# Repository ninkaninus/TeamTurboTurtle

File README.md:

# TeamTurboTurtle
This is the repository of Team Turbo Turtle! A group made for the second semester project in robotics technology at Southern University Of Denmark. The goal of the project is to automate a scalextric car to run the fastest lap on an unknown course all by itself.

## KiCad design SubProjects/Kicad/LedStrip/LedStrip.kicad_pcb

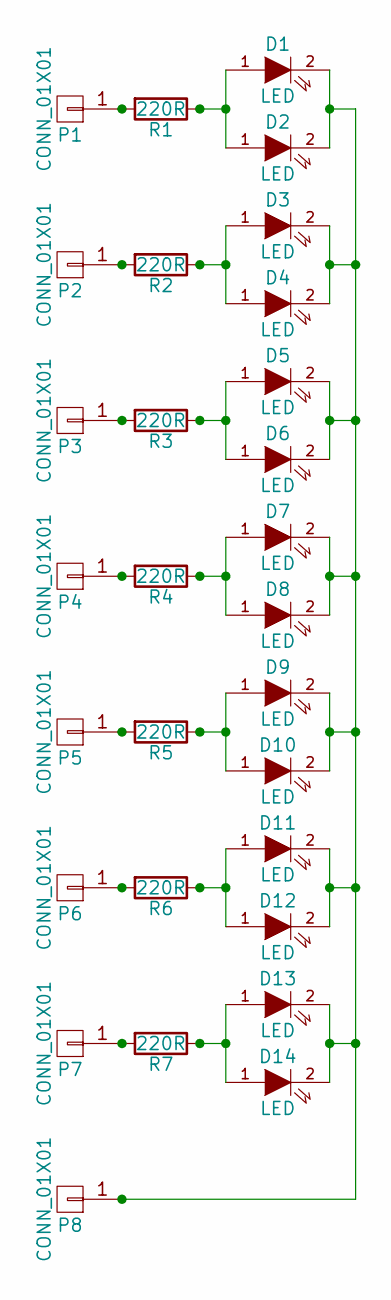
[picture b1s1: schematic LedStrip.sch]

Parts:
D1, D2, D3, D4, D5, D6, D7, D8, D9, D10, D11, D12, D13, D14: LED; LED-0805
P1, P2, P3, P4, P5, P6, P7, P8: CONN_01X01; Pin_Header_Straight_1x01
R1, R2, R3, R4, R5, R6, R7: 220R; R_0805_HandSoldering

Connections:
unnamed: D1.1 (A), D2.1 (A), R1.1
unnamed: D1.2 (K), D2.2 (K), D3.2 (K), D4.2 (K), D5.2 (K), D6.2 (K), D7.2 (K), D8.2 (K), D9.2 (K), D10.2 (K), D11.2 (K), D12.2 (K), D13.2 (K), D14.2 (K), P8.1
unnamed: D3.1 (A), D4.1 (A), R2.1
unnamed: D5.1 (A), D6.1 (A), R3.1
unnamed: D7.1 (A), D8.1 (A), R4.1
unnamed: D9.1 (A), D10.1 (A), R5.1
unnamed: D11.1 (A), D12.1 (A), R6.1
unnamed: D13.1 (A), D14.1 (A), R7.1
unnamed: P1.1, R1.2
unnamed: P2.1, R2.2
unnamed: P3.1, R3.2
unnamed: P4.1, R4.2
unnamed: P5.1, R5.2
unnamed: P6.1, R6.2
unnamed: P7.1, R7.2

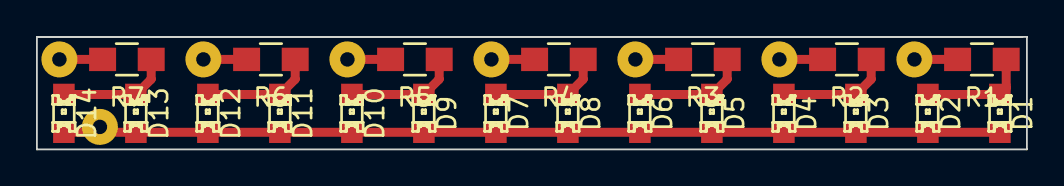
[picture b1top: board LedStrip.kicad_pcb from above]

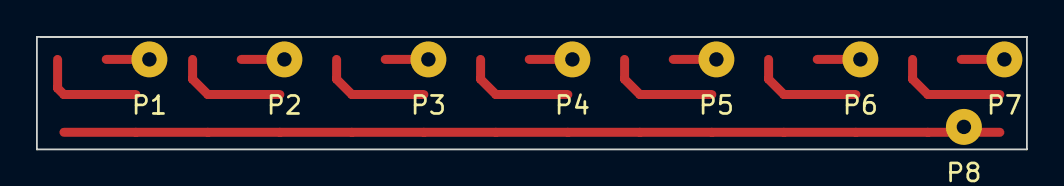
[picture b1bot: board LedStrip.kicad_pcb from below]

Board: 2 copper layers, 55.0 x 6.2 mm, 29 parts (8 on the bottom side), 15 nets.

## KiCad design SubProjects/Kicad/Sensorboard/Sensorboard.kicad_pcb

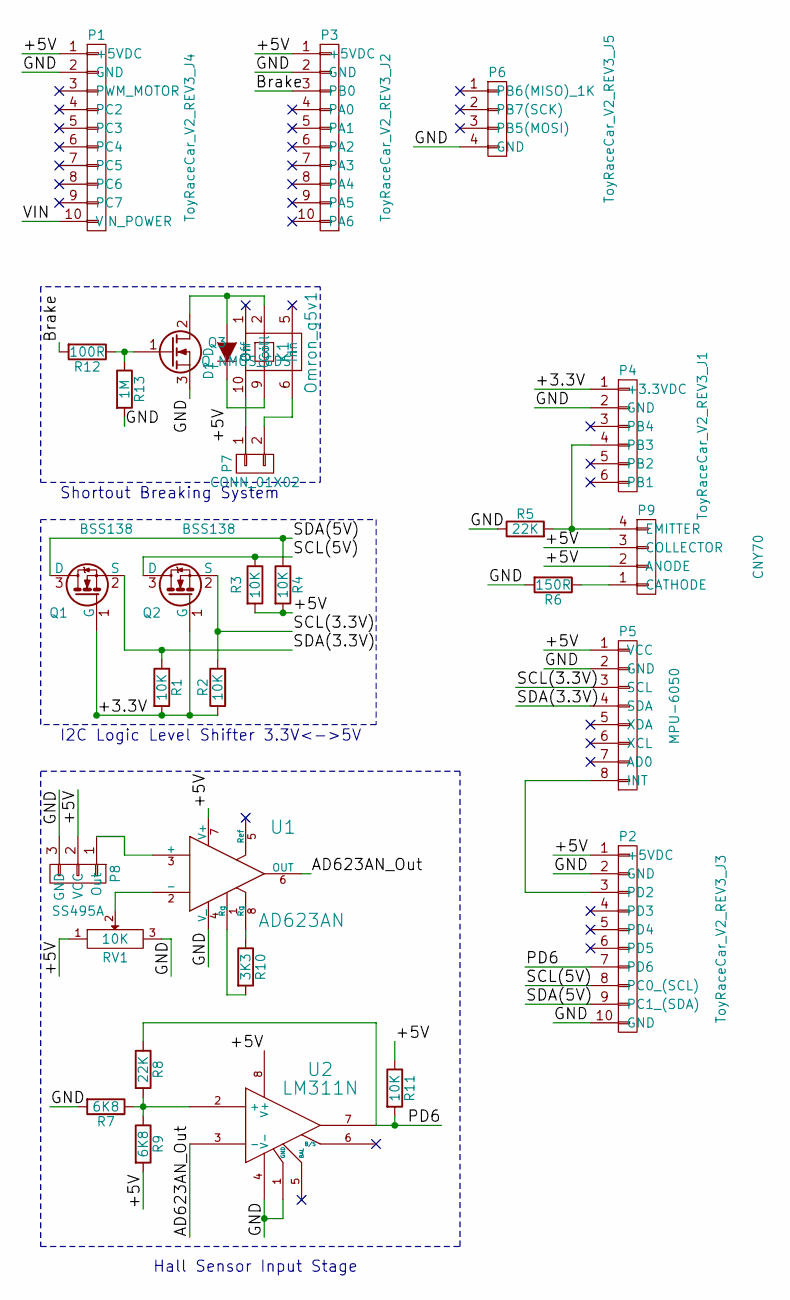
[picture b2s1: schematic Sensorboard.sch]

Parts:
D1: D; Diode_DO-35_SOD27_Horizontal_RM10
K1: Omron_g5v1; Omron-G5V1
P1: ToyRaceCar_V2_REV3_J4; Pin_Header_Straight_1x10
P2: ToyRaceCar_V2_REV3_J3; Pin_Header_Straight_1x10
P3: ToyRaceCar_V2_REV3_J2; Pin_Header_Straight_1x10
P4: ToyRaceCar_V2_REV3_J1; Pin_Header_Straight_1x06
P5: MPU-6050
P6: ToyRaceCar_V2_REV3_J5; Pin_Header_Straight_1x04
P7: CONN_01X02; Pin_Header_Angled_1x02
P8: SS495A; Pin_Header_Angled_1x03
P9: CNY70; Pin_Header_Angled_1x04
Q1, Q2: BSS138; SOT-23_Handsoldering
Q3: Q_NMOS_GDS; CASE369D
R1, R2, R3, R4, R11: 10K; R_0805_HandSoldering
R5, R8: 22K; R_0805_HandSoldering
R6: 150R; R_0805_HandSoldering
R7, R9: 6K8; R_0805_HandSoldering
R10: 3K3; R_0805_HandSoldering
R12: 100R; R_0805_HandSoldering
R13: 1M; R_0805_HandSoldering
RV1: 10K; Potentiometer_Bourns_3006P_Angular_ScrewFront
U1: AD623AN; DIP-8__300
U2: LM311N; DIP-8__300

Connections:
/+3.3V: P4.1 (+3.3VDC), Q1.1 (G), Q2.1 (G), R1.2, R2.1
/+5V: D1.2 (K), K1.9 (Coil), P1.1 (+5VDC), P2.1 (+5VDC), P3.1 (+5VDC), P5.1 (VCC), P8.2 (VCC), P9.2 (ANODE), P9.3 (COLLECTOR), R3.2, R4.2, R9.2, R11.1, RV1.1, U1.7 (V+), U2.8 (V+)
/AD623AN_Out: U1.6 (OUT), U2.3 (-)
/Brake: P3.3 (PB0), R12.2
/GND: P1.2 (GND), P2.2 (GND), P2.10 (GND), P3.2 (GND), P4.2 (GND), P5.2 (GND), P6.4 (GND), P8.3 (GND), Q3.3 (S), R5.1, R6.2, R7.2, R13.2, RV1.3, U1.4 (V_), U2.1 (GND), U2.4 (V-)
/PD6: P2.7 (PD6), R8.1, R11.2, U2.7
/SCL(3.3V): P5.3 (SCL), Q2.2 (S), R2.2
/SCL(5V): P2.8 (PC0_(SCL)), Q2.3 (D), R3.1
/SDA(3.3V): P5.4 (SDA), Q1.2 (S), R1.1
/SDA(5V): P2.9 (PC1_(SDA)), Q1.3 (D), R4.1
/VIN: P1.10 (VIN_POWER)
unnamed: D1.1 (A), K1.2 (Coil), Q3.2 (D)
unnamed: K1.6 (In), P7.2
unnamed: K1.10 (On), P7.1
unnamed: P2.3 (PD2), P5.8 (INT)
unnamed: P4.4 (PB3), P9.4 (EMITTER), R5.2
unnamed: P8.1 (Out), U1.3 (+)
unnamed: P9.1 (CATHODE), R6.1
unnamed: Q3.1 (G), R12.1, R13.1
unnamed: R7.1, R8.2, R9.1, U2.2 (+)
unnamed: R10.1, U1.8 (Rg)
unnamed: R10.2, U1.1 (Rg)
unnamed: RV1.2, U1.2 (-)

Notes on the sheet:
I2C Logic Level Shifter 3.3V<->5V
Hall Sensor Input Stage
Shortout Breaking System

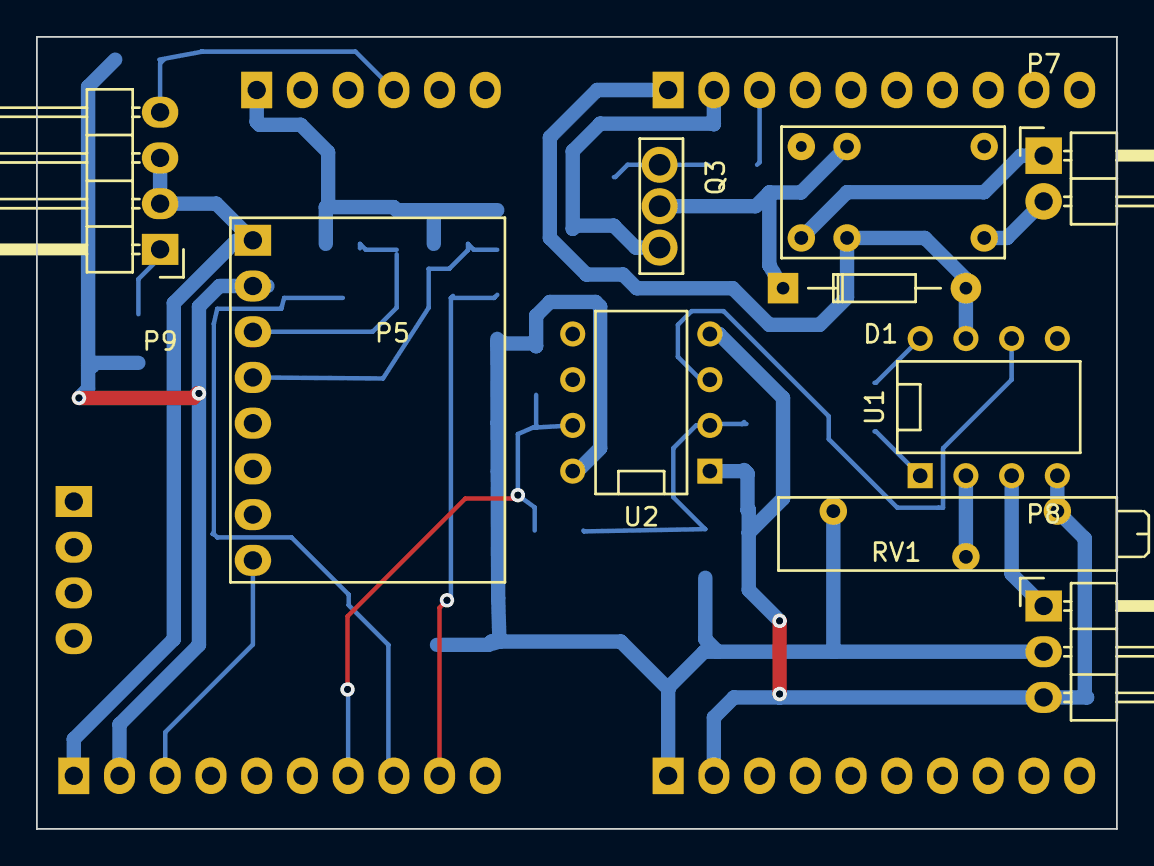
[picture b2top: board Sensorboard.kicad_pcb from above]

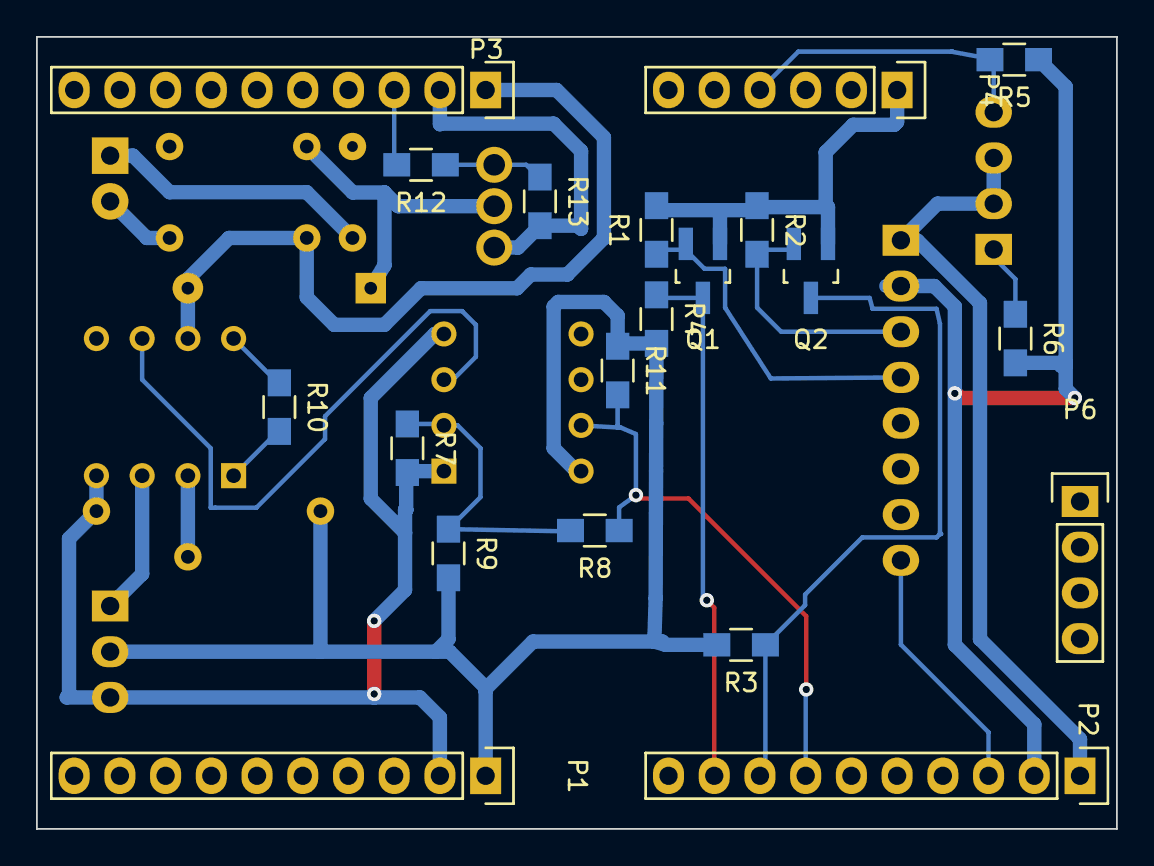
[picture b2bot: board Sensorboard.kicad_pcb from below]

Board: 2 copper layers, 60.0 x 44.0 mm, 30 parts (20 on the bottom side), 22 nets.

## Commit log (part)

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2015-02-26 Added ! behind Team Turbo Turtle
2015-02-26 Created Folder Structure #3
    I have just created the folder structure of the project.
2015-02-26 Fixed empty folders, fixes #3
    The last commit updated the folder structure, but github does not notice
    folders unless there is files in them. This fixes is by adding some
    files to each folder.
2015-02-27 BestTimefunction added to read and write from EEPROM, fixes #5
2015-02-27 old files removed
2015-02-27 comments added
2015-02-27 b command added to help
2015-02-27 Made a more usable version.
    In this version you can specify how many laps you want to sample and the
    program will generate a plot when the samples has been collected.
2015-02-27 Updated Folder Structure
2015-02-28 Just added some comments to the script
2015-02-28 Just some code enhancements. No new functionalitys added.
2015-03-01 Changed unsigned long to long in the read EEPROM function.
2015-03-04 The official test firmware to test if the board is working. If the board is working you will be able to connect to it via bluetooth and write three different commands via serial: 0 = Stop 5 = Slow Sp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
2015-03-06 Updated the makefile to support usbasp
2015-03-09 Uploaded a very usefull book for avr microcontrollers.
2015-03-09 position
2015-03-11 Began work on the sensor board
2015-03-16 Stavefejl and stuff
2015-03-16 Krav fra Preben.
2015-03-16 Made a hello world application for the bluetooth communication!
2015-03-23 Started work on the accelerometer breakout board.
2015-03-24 New master and setup
2015-03-24 master changes
2015-03-25 Updated folder structure with link folder. And populated it with links regarding PWM.
2015-03-26 Updated some documentation stuff
2015-03-26 Fuckup
2015-03-26 Fucked up again
2015-03-26 awdada
2015-03-26 Working libraries for USART and Motor control
2015-03-26 Fixed some formatting
2015-03-27 Replaced the book with the complete version
2015-03-28 Temp: Move from stationary to laptop
2015-03-28 Made some updates to the different libraries. And wrote some code to try mpu-6050. I can't get it to work. I think it has to do with the pullups
2015-04-06 First interaction with the mpu-6050. Got it to return it's own address.
2015-04-06 Definitions for the accelerometer and a link explaining the operation of it.
2015-04-07 Working I2C communication with the MPU-6050! As of now the code just outputs the raw 16 bit binary value of the gyroes z-axis, to the terminal.
2015-04-07 Commented and cleaned the code
2015-04-07 These needs to be added to an ignore file
2015-04-07 Added some nice links for the mpu-6050
2015-04-08 Link to the official documentation for the avr assembler
2015-04-09 Update Nudel Liste.txt
    william +1
2015-04-09 Update Nudel Liste.txt
    daniel +1
2015-04-09 gitignore added
2015-04-09 .gitignore added
2015-04-09 Stuff
2015-04-13 Added a mapping list of the SRAM memory
2015-04-13 Setup af OCIE0 og INT0 interrupt
2015-04-13 Opsætning af Timer0 til 1[ms] output compare match
2015-04-13 datasheet
2015-04-14 Working example
2015-04-14 Macro setup for Timer0 init
2015-04-14 Interrupt vector for Timer0 output compare interrupt
2015-04-14 Update Nudel Liste.txt
    NUUDLES!
2015-04-14 Updated some libraries to support interrupts. And created a way to keep track of time
2015-04-16 Update Nudel Liste.txt
    Snuppet to i dag
2015-04-17 Initial setup of lap time interrupt routine. Further polish still needed
2015-04-17 Added memory locations for latest lap time and changed a few names.
    Fixed issue where the external interrupt would trigger more than once by adding delay.
2015-04-20 Commenting
2015-04-20 Oprettede et dokument
2015-04-20 Første version
2015-04-20 Update Nudel Liste.txt
    William +2
2015-04-20 update - Began adding connections
2015-04-21 Opdateret AI kode
2015-04-22 First try at using kicad to model the board
2015-04-23 Tilføjet prototype AI til efter den første omgang. Der mangler en del AI, men denne version burde virke efter justeringer af accelerometer værdier + bugfixing
2015-04-23 Updated the pcb even more
2015-04-23 Working lap timer code + hardware
2015-04-25 Board is designed with MPU6050, Logic Level Shifter and lap counter circuitry. Done for now.
2015-04-26 Working interrupt. Set up as a repeater for now. Just sends back the ASCII character you send.
2015-04-27 Added another connector for the hall sensor
2015-04-27 Models for connectors
2015-04-27 Broke the protocol
2015-04-27 The protocol is now living up to the requirment of the set commands.
2015-04-27 Cleanup after merge with the Communication Protocol branch
2015-04-28 Indsat konstant definitioner, og ryddet lidt op i koden.
2015-04-28 Nearly final design. Just missing the mounting holes
2015-04-28 Added two 2.5mm mounting holes. We need to check if that is the actual size, but atleast they are in the correct position now.
2015-04-29 Finished print and generated layers
2015-04-29 Quick test script to test the newly mounted sensor board
2015-04-30 Input Capture setup and interrupt routines
2015-04-30 Bedre værdi for hall
2015-04-30 Fixes
2015-04-30 Commented the communication protocol script
2015-04-30 Cleanup and commenting
2015-05-02 Working % set of the motor speed.
2015-05-02 Cleanup - Noticed some debugging USART messages and deleted them.
2015-05-03 Implemented the option to choose a port on startup
2015-05-03 Added some more usefull links
2015-05-04 Ændret navn på filen og indsat ram position til brug ved mapping Også andre små ændringer
2015-05-04 i dunno
2015-05-04 Weird stuff is happening
2015-05-04 Working Code
2015-05-05 Har byttet filen ud med noget jeg kan ændrer i. Har benyttet Ram addresser, således at der ikke bruges så mange registre.
2015-05-05 Ved ikke hvorfor det her ikke kom med.
2015-05-05 Updated links and made a simple litte application
2015-05-06 Små rettelser
2015-05-06 Wheelspeed fix mk1. Identificering af lorten og efterfølgende afskaffelse af denne
2015-05-06 Random wheelspeed crap
2015-05-06 Trying out some code
2015-05-07 aQWfsrdghm
2015-05-07 Links and stuff
2015-05-07 Merged Wheelspeed code into AI and cleaned it all up
2015-05-09 Doing stuff
2015-05-11 Updated some stuff for easier debugging of the now again working car.
2015-05-11 Har tilføjet hastighed_D til hastigheds outputtet
2015-05-11 Mindre ændring
2015-05-11 Added again
2015-05-11 grrrr
2015-05-11 Har implimenteret hastigheds kontrol i hall interrupted.
2015-05-11 GUI update
2015-05-11 Working serial interface in GUI
2015-05-12 Port list created
2015-05-13 Wheelspeed der kører på INT1 interrupt
2015-05-13 Benytter nu periode, samt en reference hastighed. Alle værdier skal justeres betydeligt
2015-05-13 Started working on an emulator script for developing the software
2015-05-13 Har rettet mindre fejl, samt gjord det klart hvad der skal ændres.
2015-05-14 Made some changes to compile on windows
2015-05-14 Somewhat working code. Lap counter interrupts are working. Hall sensor is work in progress. Currently working on maintaining a steady speed.
2015-05-15 rapport started
2015-05-15 added -lst to git ignore
2015-05-15 gitignore updated
2015-05-15 Better start stop buttons
2015-05-15 Ændret mit navn
2015-05-15 afsnit folder added
2015-05-16 Stuff is working. Able to pull data although very unstable
2015-05-16 Semi working concept.
2015-05-18 Branched out some code to subclasses. Created a seperate thread for data collection. Optimized some things.
2015-05-18 Hastighedstest med forskellige inputs til OCR alt efter hvor langt bilen er fra den ideelle hastighed
2015-05-18 We did the stuff and it worked, but then we did the other stuff, and it broke
2015-05-18 Har ryddet op i koden. Banetype bestemmelsen er flyttet over i AI_Gyro, og benyttes nu kun i HALL interrupt. Dette burde få det til at virke.
2015-05-18 More implementation of the com protocol into the program.
2015-05-19 Added some com values
2015-05-19 Fixed a bug with a duplicate receive command
2015-05-20 Forbedret hastighedskontrol
2015-05-20 just do it
2015-05-20 Småændringer i tachometer stuff
2015-05-20 Moved the value updates to the command get's
2015-05-20 Har flyttet section include fra master til Pageinclude.tex
2015-05-20 Updated SRAM addresses: Removed unnecessary addresses.
2015-05-20 Tilføjet billede af schmitt triggeren
2015-05-20 Clean slate
2015-05-20 Nye filer
2015-05-20 Updated the protocol to handle communication 1 byte at a time instead of 3 at a time. This should help to stop sync errors. Still need to do it for the program though
2015-05-21 -Protocol is updated and working -GUI now handles signed numbers
2015-05-21 -Protocol tweaks -Able to save data sets and plot dem individually. Although there is a timing issue as of now
2015-05-21 der er sket noget
2015-05-22 det går godt
2015-05-22 Lots of improvement
2015-05-23 En afprøvningsmode af bremsen der rent faktisk giver mening og virker
2015-05-23 Har tilføjet to macros til at ændre bits i SREG_1, og en anden mulig delay funktion i Time der holder øje med bit 7 i SREG_1
2015-05-23 Updated pcb with the brake system
2015-05-23 Har skiftet input ben til bremsen
2015-05-24 Har rystet en fortryllende hastighedskontrol ud af ærmet. Den kan også lave kaffe!
2015-05-24 Det her virker, hvis det går galt så er det her udgangspunktet vi går tilbage til
2015-05-24 more done
    Gemmer nu det første stykke til sidst, med mindre det er samme type som det sidste, så lægges længderne sammen.
2015-05-24 Lot of optimization
2015-05-24 Working
2015-05-24 Har fedtet en lille smule med Hastigheds_kontrol. Mangler stadigvæk at finde nogle ordentlige værdier der kan bruges under alle forhold.
2015-05-24 Har skrevet en smule software shizzle
2015-05-24 Awesome config
2015-05-24 Epic
2015-05-25 Sidehoved opdateret med dato
2015-05-25 Prebens navn opdateret på forsiden
2015-05-25 Litterratur liste startet, der mangler stadig noget
2015-05-25 Lidt mere software hardware
2015-05-25 - Første halvdel omkring kommunikationsprotokollen er skrevet færdig - Har indsat et ekstra afsnit under software, der beskriver generelle funktionaliteter som vi gør brug af. Titlen er stadigvæk w.i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
2015-05-25 Added ignores to remove the generated files for master
2015-05-26 -Beskrevet størstedelen af kommunikations protokolen
2015-05-26 Accelramometer startet
2015-05-26 wrapfig includet
2015-05-26 Hardware updated med wrapping og minipage
2015-05-26 Photos added
2015-05-26 -Billede af logic level shifter -Færdig med at skrive om protokollen
2015-05-26 billeder af top og bund af printet
2015-05-26 Har ændret et lille men vigtigt minus til et plus :D
2015-05-26 Har skrevet en smule på hastighedskontrollen
2015-05-26 AI added, GUI in new file Setup changed
2015-05-26 Daniels kode opdateret og indholdsfortegnelsen gjort mindre
2015-05-26 -Skrevet underliggende funktioner færdigt
2015-05-26 Har tilføjet flow chart til hastighedskontrollen. Sat et par kommaer hist og her
2015-05-26 Har tilføjet lækker lækker bremsegraf og et lille afsnit om bremsetests
2015-05-26 Har hentet accellerometeret tilbage fra de døde
2015-05-26 GUI moved from AI to Software
2015-05-26 Fisker mere dødt op
2015-05-26 Ændre noget i elektromagnet og en fejl i software
2015-05-26 -Færdiggjort generel struktur
2015-05-26 Skrevet print færdigt
2015-05-26 Har skrevet en hel masse om tests og en masse andet lir
2015-05-26 Ændret nogle små fejl
2015-05-26 Små ændringer i elektromagnet
2015-05-26 - skrevet afsnit om GUI
2015-05-26 Har fixet et par kommafejl, reference og labels
2015-05-26 Har rettet lortefejl
2015-05-26 Photo moved
2015-05-26 started on logic level shifter
2015-05-26 , added
2015-05-26 Der kommer lige lidt AI ændringer
2015-05-26 -Fixed some include stuff in the AI -Wrote a little intro to Funktioner
2015-05-26 Har rettet et par stave/komma-fejl
2015-05-26 , done in software
2015-05-26 Problemformulering, Krav og projektafgrænsning
2015-05-26 Tidsplan
2015-05-26 Discription
2015-05-27 safd
2015-05-27 tidsplan ændret
2015-05-27 Færdig ish konklusion
2015-05-27 40 SIDER
2015-05-27 billag added
2015-05-27 CD started
2015-05-27 folder structure changed
2015-05-27 Lessened the top and bottom whitespace before sections, subsections and subsubsections
2015-05-27 Slettet lidt sjov og ballade
2015-05-27 Changed some stuff
2015-05-27 Pushing Daniel to the limit
2015-05-27 Mangler lige en gennemlæsning
2015-05-27 rettet i cd listen
2015-05-28 Har tilføjet 4 programmer til cylon scanneren og push/poppet nogle flere registre
2015-05-28 LEdstrip
2015-05-28 Fixet taevelig lap fejl
2015-05-29 Gemt hastighederne i SRAM istedet
